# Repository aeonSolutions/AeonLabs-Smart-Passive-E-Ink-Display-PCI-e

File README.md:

[PCB-Prototyping-Catalogue](https://github.com/aeonSolutions/PCB-Prototyping-Catalogue)  >>  [Smart LCD Touch Displays](https://github.com/aeonSolutions/PCB-Prototyping-Catalogue/tree/main/Smart%20LCD%20Touch%20Displays)  >>  Smart Passive E-Ink Display-PCI-e

<br>

# Smart Passive E-Ink Display-PCI-e
A PCB for a 2.13" E-Ink Display with PCI-e connection. Requires #no #power an can be configured using @AeonlabsS E-Ink Configuration Device (#EInkCD). Suitable for #commerce or #warehouse shelves for #labelling or #price tagging. Total cost, including the E-Ink Display starts at only 10 euros. Already assembled.

*Don't forget to LIKE , SHARE and subscribe the free whatsApp group* and if you liked this PCB consider buying me a cup of coffee. Links below.

### Status
  Waiting to be tested.

If you already tested this PCB send me a message. Thank you

## Versions
### AeonLabs improved Hot Solder Reflow Plate
- revision 2.x (ToDo)
  - Android App to view and control the E-Ink passive Display

- revison 1.x
  - PCB for the 2.13" E-Ink Passive Display. No batteries or power required.

  PCB fabrication of June 2022 (reviision 1.1) was sponsored by [PCBWay](www.pcbway.com)
  
PCB fabrication of June 2022 (reviision 2.1) was sponsored by [PCBWay](www.pcbway.com)

### alternatively if you do not want to build a PCB by yourself, you can buy here:

The price will be around 30eur plus postage fees.
(I will also deliver the assembled PCB with all the components in place at an aditonal cost).

## Liked it ? Get a Free PCB for yourself
Send me your Device or hardware and i will design a custom PCB for it. Free of charge. Contact-me on WhatsApp or email for more info. 

## Q&A WhatsApp Group
If you have any Questions or simply  like this kind of projects and want to stay updated with the latest research ideas and prototypes during the day and week, join the WhatsApp Group
[LDAD Lab & Prototyping](https://chat.whatsapp.com/FkNC7u83kuy2QRA5sqjBVg)

________________________________________________________________________________________________________________
## [Go back to main catalogue page](https://github.com/aeonSolutions/PCB-Prototyping-Catalogue)
________________________________________________________________________________________________________________

#### PCB Parts list:
- 2.13" E-Ink Display: https://s.click.aliexpress.com/e/_9gJUhJ
- FPC 24 pin connector: https://s.click.aliexpress.com/e/_AEUWtr
- FPC 10 pint connector: https://s.click.aliexpress.com/e/_AEUWtr
- SMD capacitors: https://s.click.aliexpress.com/e/_Asa5qd

<br />
<br />

______________________________________________________________________________________________________________________________

### PCB Conceptualization and Design
<p align="center">

</p>

<br />
<br />

### PCB Fabrication
<p align="center">

</p>

<br />
<br />

## Author

You can get in touch with me on my LinkedIn Profile:

#### Miguel Tomas

You can also follow my GitHub Profile to stay updated about my latest projects: 

<br>

### Be supportive of my dedication and work towards technology education and buy me a cup of coffee
The PCB Desgin Files i provide here for anyone to use are free. If you like this Smart Device or use it, please consider buying me a cup of coffee, a slice of pizza or a book to help me study, eat and think new PCB design files.

<p align+"left">

<br>

</p>

<br />

### Make a donation on Paypal
Make a donation on paypal and get a TAX refund*.

<br>

### Support all these open hardware projects and become a patreon  
Liked any of my PCB KiCad Designs? Help and Support my open work to all by becomming a LDAD Patreon.
In return I will give a free PCB design in KiCad to all patreon supporters. To learn more go to patreon.com. Link below.

<br />
<br />

______________________________________________________________________________________________________________________________
### License

Before proceeding to download any of AeonLabs software solutions for open-source development and/or PCB hardware electronics development make sure you are choosing the right license for your project. See [AeonLabs Solutions for Open Hardware & Source Development](https://github.com/aeonSolutions/PCB-Prototyping-Catalogue/wiki/AeonLabs-Solutions-for-Open-Hardware-&-Source-Development) for more information. 

______________________________________________________________________________________________________________________________

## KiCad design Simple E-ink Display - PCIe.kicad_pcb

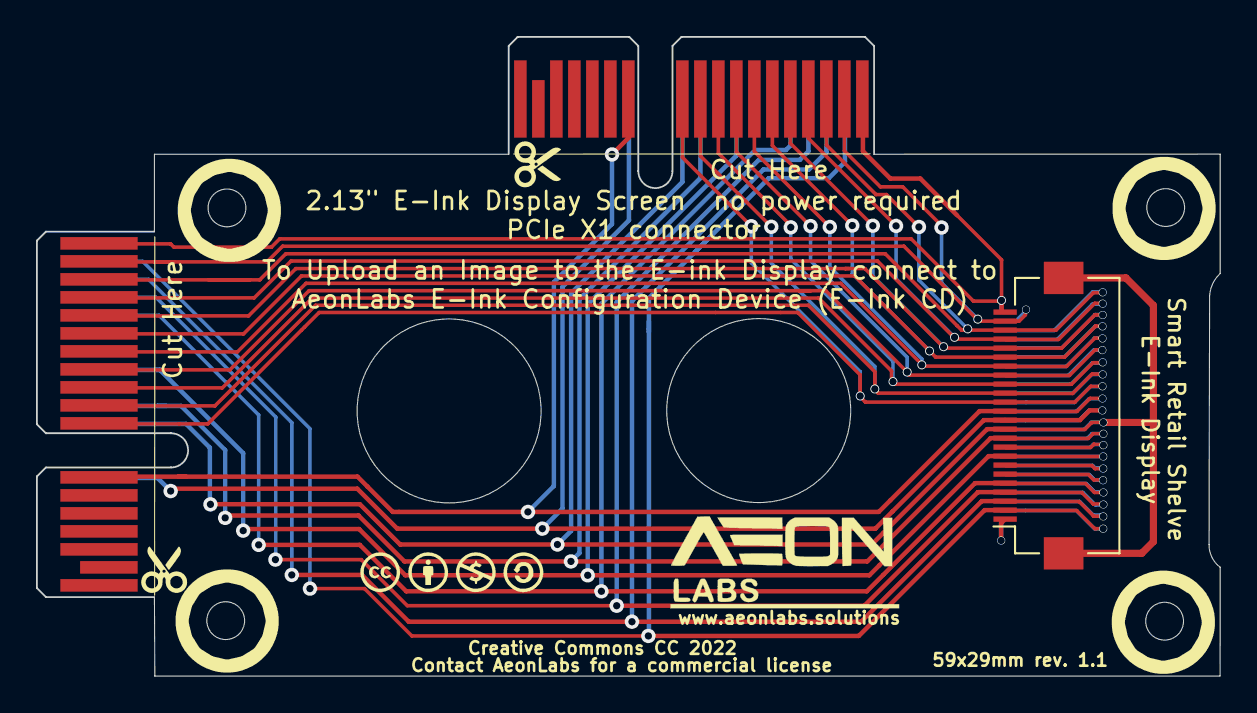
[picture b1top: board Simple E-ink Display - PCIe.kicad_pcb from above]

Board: 2 copper layers, 65.7 x 35.5 mm, 8 parts (1 on the bottom side), 20 nets.

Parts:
H1, H2, H3, H4: MountingHole; MountingHole_2.1mm
J1, J3: Bus_PCI_Express_x1_Generic; BUS_PCIexpress_x1 6.5MM
J2, J2#2: Conn_01x24_Female; Hirose_FH12-24S-0.5SH_1x24-1MP_P0.50mm_Horizontal

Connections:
unnamed: J1.A2, J2.2, J2#2.2, J3.A2
unnamed: J1.A3, J2.3, J2#2.3, J3.A3
unnamed: J1.A4, J2.4, J2#2.4, J3.A4
unnamed: J1.A5, J2.5, J2#2.5, J3.A5
unnamed: J1.A8, J2.8, J2#2.8, J3.A8
unnamed: J1.A10, J2.10, J2#2.10, J3.A10
unnamed: J1.A11, J2.11, J3.A11
unnamed: J1.A12, J2.12, J2#2.12, J3.A12
unnamed: J1.B1, J2.24, J2#2.24, J3.B1
unnamed: J1.B2, J2.23, J2#2.23, J3.B2
unnamed: J1.B3 (b3), J2.22, J2#2.22, J3.B3 (b3)
unnamed: J1.B4, J2.21, J2#2.21, J3.B4
unnamed: J1.B5, J2.20, J2#2.20, J3.B5
unnamed: J1.B6, J2.19, J2#2.19, J3.B6
unnamed: J1.B7, J2.18, J2#2.18, J3.B7
unnamed: J1.B8, J2.17, J2#2.17, J3.B8
unnamed: J1.B9, J2.16, J2#2.16, J3.B9
unnamed: J1.B10, J2.15, J2#2.15, J3.B10
unnamed: J1.B11, J2.14, J2#2.11, J2#2.14, J3.B11
unnamed: J1.B12, J2.13, J2#2.13, J3.B12

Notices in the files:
Simple E-ink Display - PCIe.kicad_pcb:
Creative Commons CC 2022
